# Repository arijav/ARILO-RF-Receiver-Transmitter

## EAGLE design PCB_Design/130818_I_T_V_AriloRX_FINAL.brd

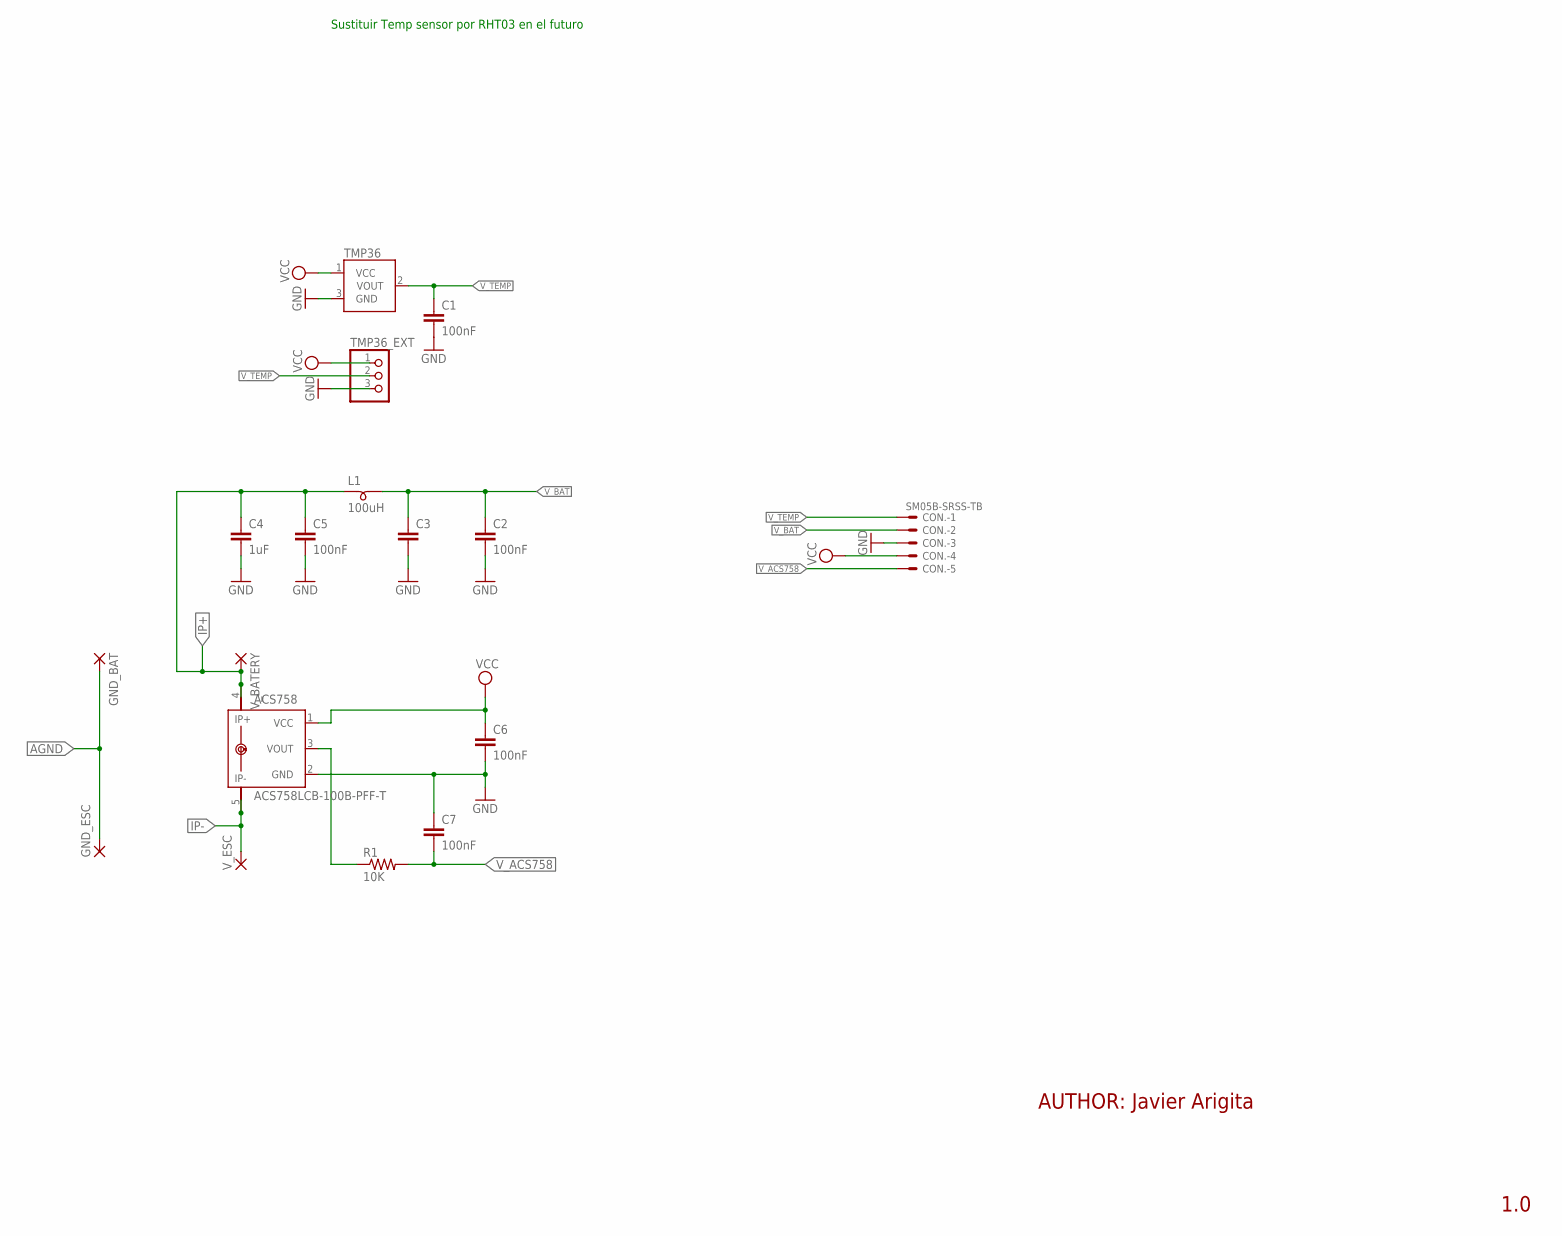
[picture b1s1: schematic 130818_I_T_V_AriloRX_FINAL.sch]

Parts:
ACS758: ACS758LCB-100B-PFF-T; CB-PFF
C1, C2, C5, C6, C7: 100nF; C0805
C3: C-EUC3216; C3216
C4: 1uF; C3216
CON.: SM05B-SRSS-TB
GND_BAT: SMD5; SMD2,54-5,08
GND_ESC: SMD5; SMD2,54-5,08
L1: 100uH; SM-B5
R1: 10K; R0805
TMP36: TMP36GT9; TO-92
TMP36_EXT: PINHD-1X3; 1X03
V_BATERY: SMD5; SMD2,54-5,08
V_ESC: SMD5; SMD2,54-5,08

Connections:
AGND: GND_BAT.1, GND_ESC.1
GND: ACS758.2 (GND), C1.2, C2.2, C3.2, C4.2, C5.2, C6.2, C7.1, CON..3, TMP36.3 (GND), TMP36_EXT.3
IP+: ACS758.4 (IP+), ACS758.IP+1, C4.1, C5.1, L1.1, V_BATERY.1
IP-: ACS758.5 (IP-), ACS758.IP-1, V_ESC.1
unnamed: ACS758.3 (VOUT), R1.1
VCC: ACS758.1 (VCC), C6.1, CON..4, TMP36.1 (VCC), TMP36_EXT.1
V_ACS758: C7.2, CON..5, R1.2
V_BAT: C2.1, C3.1, CON..2, L1.2
V_TEMP: C1.1, CON..1, TMP36.2 (VOUT), TMP36_EXT.2

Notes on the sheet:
AUTHOR: Javier Arigita
1.0
Sustituir Temp sensor por RHT03 en el futuro

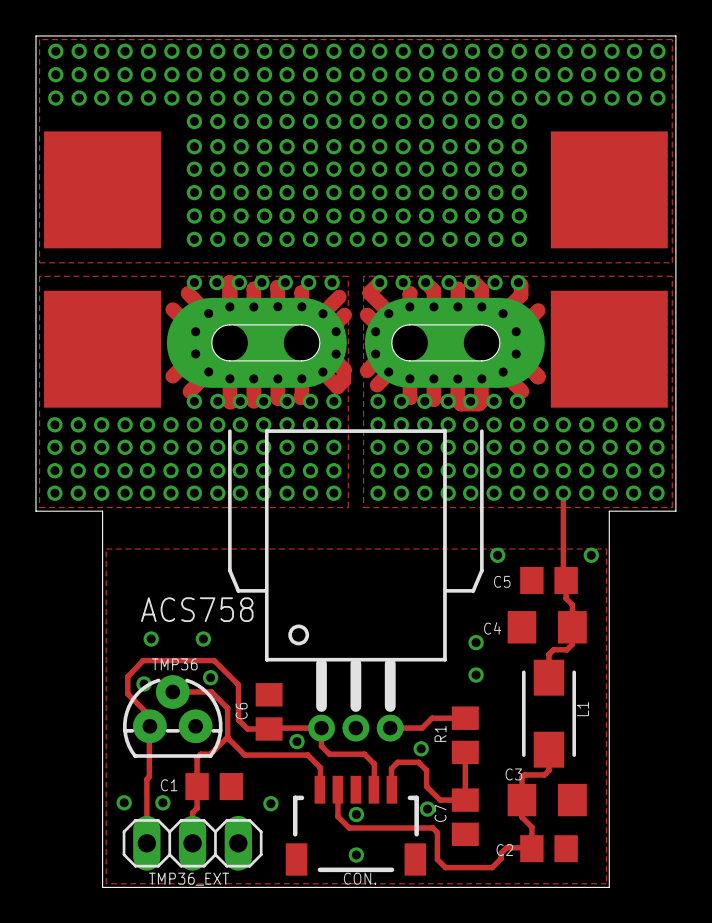
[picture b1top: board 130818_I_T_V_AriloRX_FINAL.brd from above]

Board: 2 copper layers, 35.6 x 47.3 mm, 17 parts (0 on the bottom side), 9 nets.

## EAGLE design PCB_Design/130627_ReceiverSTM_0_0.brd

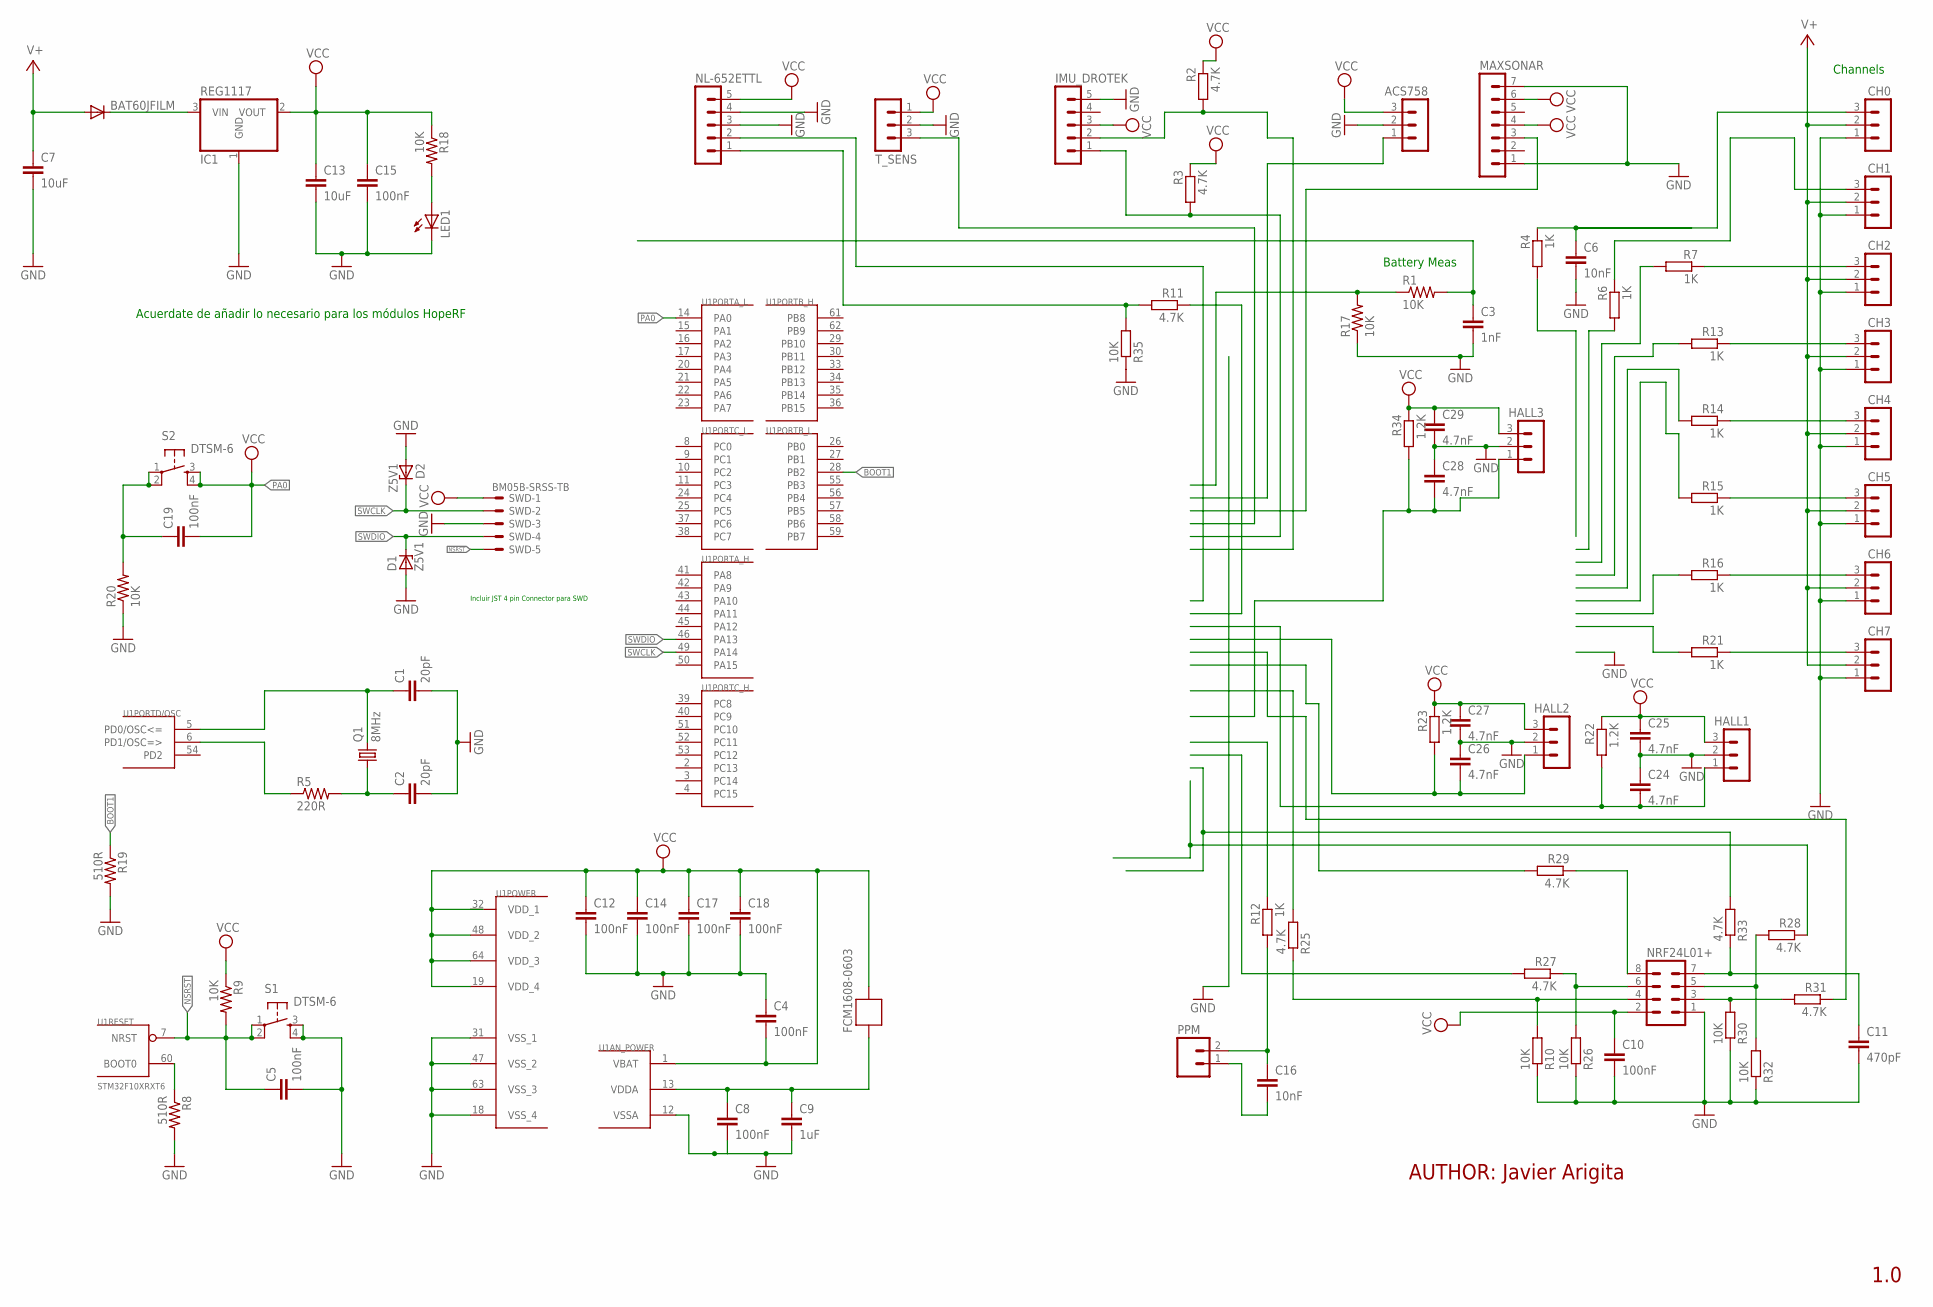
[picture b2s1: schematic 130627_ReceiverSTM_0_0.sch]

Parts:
ACS758: MA03-1
BAT60JFILM: DIODE-SOD323-R; SOD323-R
C1, C2: 20pF; C0805
C3: 1nF; C0805
C4, C5, C8, C10, C12, C14, C15, C17, C18, C19: 100nF; C0805
C6, C16: 10nF; C025-030X050
C7, C13: 10uF; C3216
C9: 1uF; C3216
C11: 470pF; C025-030X050
C24, C25, C26, C27, C28, C29: 4.7nF; C025-030X050
CH0, CH1, CH2, CH3, CH4, CH5, CH6, CH7: MA03-1
D1, D2: Z5V1; SOD80C
FCM1608-0603: FERRITE-BEAD; R0603
HALL1, HALL2, HALL3: MA03-1
IC1: REG1117; SOT223
IMU_DROTEK: MA05-1
LED1: LED0805; CHIPLED_0805
MAXSONAR: MA07-1
NL-652ETTL: MA05-1
NRF24L01+: MA04-2
PPM: M02; 02P
Q1: 8MHz; SM49
R1, R9, R17, R18, R20: 10K; R0805
R2, R3, R11, R25, R27, R28, R29, R31, R33: 4.7K; 0204/7
R4, R6, R7, R12, R13, R14, R15, R16, R21: 1K; 0204/7
R5: 220R; R0805
R8, R19: 510R; R0805
R10, R26, R30, R32, R35: 10K; 0204/7
R22, R23, R34: 1.2K; 0204/7
S1, S2: DTSM-6
SWD: BM05B-SRSS-TB
T_SENS: MA03-1
U1: STM32F10XRXT6; TQFP64

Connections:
BOOT1: R19.1, U1.28 (PB2)
GND: ACS758.2, C1.2, C2.2, C3.2, C4.1, C5.2, C6.2, C7.2, C8.2, C9.2, C10.2, C11.2, C12.2, C13.2, C14.2, C15.2, C17.2, C18.2, C24.1, C25.2, C26.1, C27.2, C28.1, C29.2, CH0.1, CH1.1, CH2.1, CH3.1, CH4.1, CH5.1, CH6.1, CH7.1, D1.A, D2.A, HALL1.2, HALL2.2, HALL3.2, IC1.1 (GND), IMU_DROTEK.5, LED1.C, MAXSONAR.1, MAXSONAR.7, NL-652ETTL.3, NL-652ETTL.4, NRF24L01+.1, R8.2, R10.1, R17.1, R19.2, R20.1, R26.1, R30.1, R32.1, R35.1, S1.3, S1.4, T_SENS.2, U1.12 (VSSA), U1.18 (VSS_4), U1.31 (VSS_1), U1.47 (VSS_2), U1.63 (VSS_3)
MAX_BRIDGE: NL-652ETTL.2
unnamed: C1.1, Q1.2, U1.5 (PD0/OSC<=)
unnamed: R5.1, U1.6 (PD1/OSC=>)
unnamed: C2.1, Q1.1, R5.2
unnamed: R8.1, U1.60 (BOOT0)
unnamed: C19.1, R20.2, S2.1, S2.2
unnamed: ACS758.3, C25.1, C27.1, C29.1, HALL1.3, HALL2.3, HALL3.3, IMU_DROTEK.3, MAXSONAR.4, MAXSONAR.6, NL-652ETTL.5, R2.1, R3.1, R22.1, R23.1, R34.1, T_SENS.1
unnamed: C16.2, PPM.1
unnamed: IMU_DROTEK.2, R2.2
unnamed: LED1.A, R18.2
unnamed: C28.2, HALL3.1, R34.2
unnamed: BAT60JFILM.C, IC1.3 (VIN)
unnamed: C24.2, HALL1.1, R22.2
unnamed: C3.1, R1.2
unnamed: C8.1, C9.1, FCM1608-0603.2, U1.13 (VDDA)
unnamed: NRF24L01+.4, R10.2, R25.1
unnamed: NRF24L01+.3, R30.2, R31.2
unnamed: C16.1, PPM.2, R12.2
unnamed: NL-652ETTL.1, R11.2, R35.2
unnamed: IMU_DROTEK.1, R3.2
unnamed: C26.2, HALL2.1, R23.2
unnamed: R1.1, R17.2
unnamed: NRF24L01+.8, R29.1
unnamed: NRF24L01+.6, R26.2, R27.1
unnamed: NRF24L01+.5, R28.2, R32.2
unnamed: C11.1, NRF24L01+.7, R33.1
unnamed: C6.1, CH0.3, R4.1
unnamed: CH1.3, R6.1
unnamed: CH2.3, R7.1
unnamed: CH3.3, R13.1
unnamed: CH4.3, R14.1
unnamed: CH5.3, R15.1
unnamed: CH6.3, R16.1
unnamed: CH7.3, R21.1
NSRST: C5.1, R9.2, S1.1, S1.2, SWD.5, U1.7 (NRST)
PA0: C4.2, C10.1, C12.1, C13.1, C14.1, C15.1, C17.1, C18.1, C19.2, FCM1608-0603.1, IC1.2 (VOUT), NRF24L01+.2, R9.1, R18.1, S2.3, S2.4, U1.1 (VBAT), U1.14 (PA0), U1.19 (VDD_4), U1.48 (VDD_2), U1.64 (VDD_3)
SWCLK: D2.C, SWD.2, SWD.3, U1.49 (PA14)
SWDIO: D1.C, SWD.4, U1.46 (PA13)
V+: BAT60JFILM.A, C7.1, CH0.2, CH1.2, CH2.2, CH3.2, CH4.2, CH5.2, CH6.2, CH7.2
VCC: SWD.1
VDD_1: U1.32 (VDD_1)

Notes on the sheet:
Battery Meas
Acuerdate de añadir lo necesario para los módulos HopeRF
AUTHOR: Javier Arigita
1.0
Channels
Incluir JST 4 pin Connector para SWD

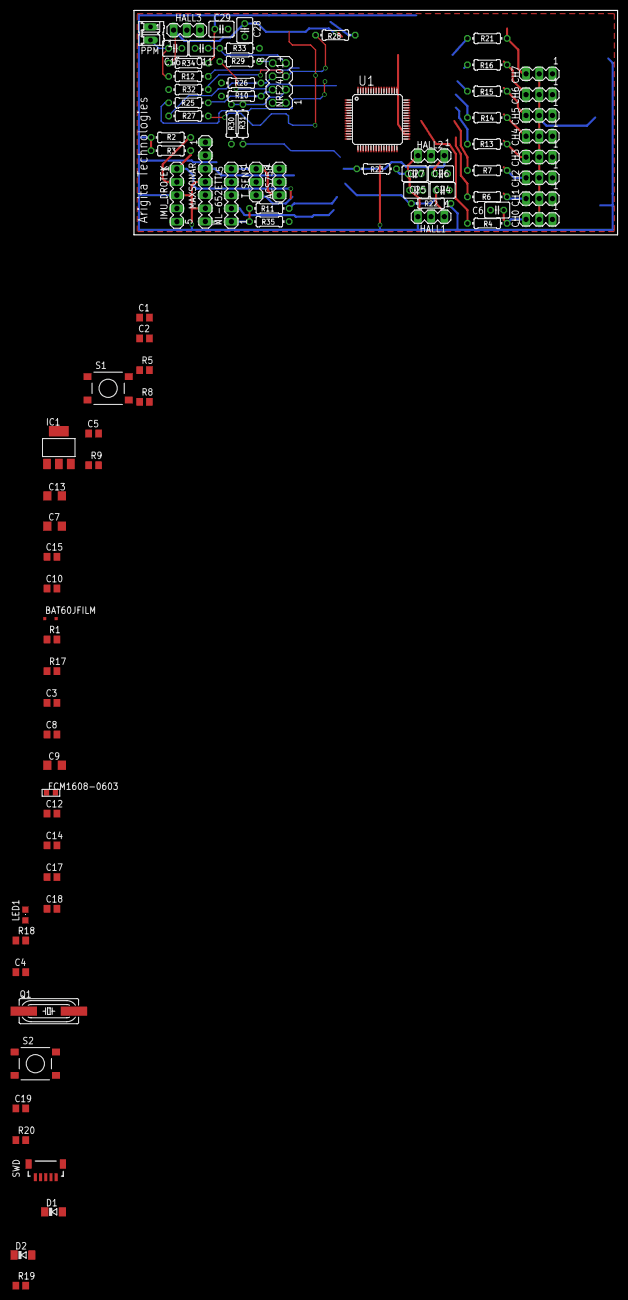
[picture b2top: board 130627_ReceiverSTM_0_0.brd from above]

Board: 2 copper layers, 93.0 x 43.2 mm, 88 parts (0 on the bottom side), 40 nets.

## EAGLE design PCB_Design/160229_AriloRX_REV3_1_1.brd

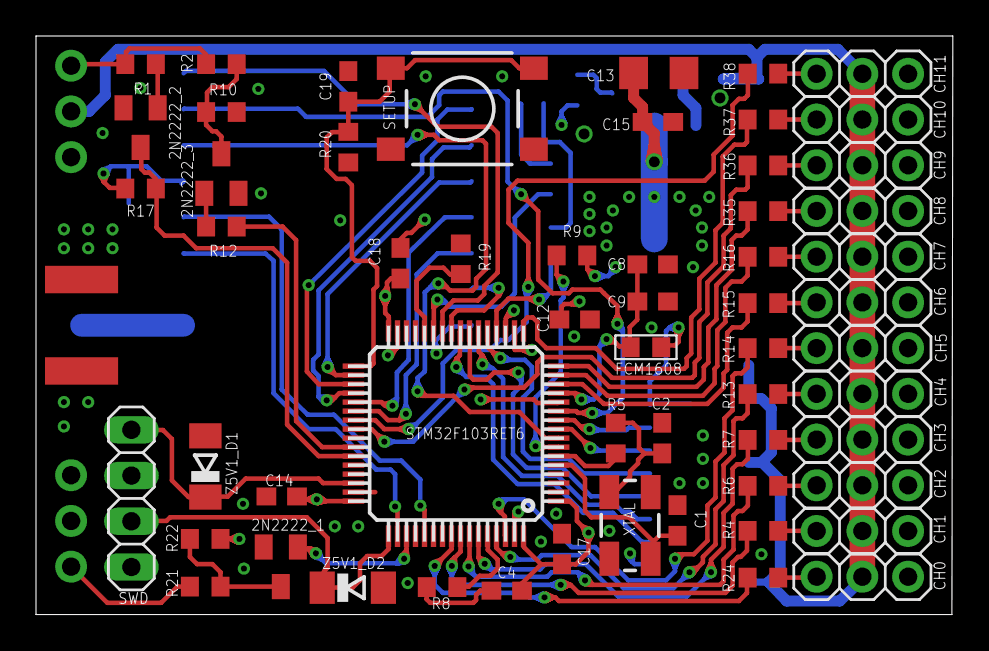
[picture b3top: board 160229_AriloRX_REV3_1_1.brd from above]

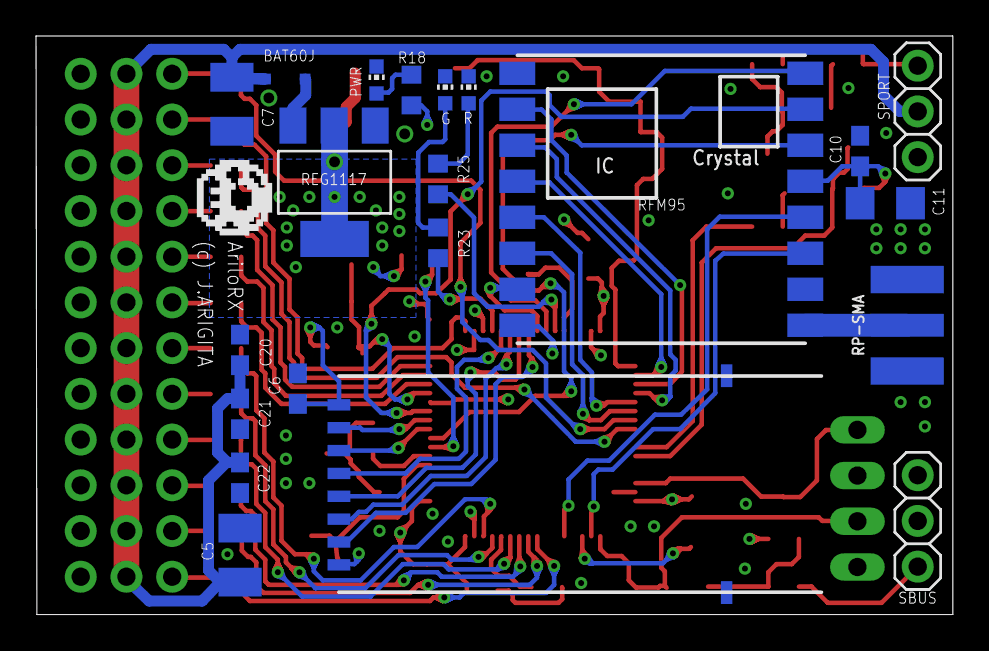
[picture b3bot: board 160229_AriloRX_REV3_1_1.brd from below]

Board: 4 copper layers, 50.9 x 32.1 mm, 79 parts (21 on the bottom side), 70 nets.

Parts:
2N2222_1, 2N2222_2, 2N2222_3: SOT23-BEC
BAT60J: SOD323-R
C1, C2: 12pF; RESISTOR_C0603
C4, C6, C8, C10, C12, C14, C15, C17, C18, C19, C20: 100nF; RESISTOR_C0603
C5: SMC_B
C7: 100uF; SMC_B
C9: 1uF; RESISTOR_C0603
C11, C13: 10uF; RESISTOR_C3216
C21: 10nF; RESISTOR_C0603
C22: 1nF; RESISTOR_C0603
CH0, CH1, CH2, CH3, CH4, CH5, CH6, CH7, CH8, CH9, CH10, CH11: 1X03
FCM1608: R0603
G: CHIP-LED0603
NRF24L01_SMD: NRF24L01+_NRF24L01_SMDSMD; NRF24L01+_NRF24L01_SMD
PWR: LED_CHIP-LED0603
R: CHIP-LED0603
R1, R9, R18, R20: 10K; RCL_R0603
R2, R4, R6, R7, R10, R12, R13, R14, R15, R16, R21, R22, R24, R35, R36, R37, R38: 1K; RCL_R0603
R5: 80R; RCL_R0603
R8, R19: 510R; RCL_R0603
R17: 4.7K; RCL_R0603
R23, R25: 220; RCL_R0603
REG1117: REG1117; SOT223
RFM95: RFM95W_MISIEK_RFM95WSMD; RFM95W_MISIEK_RFM95W_SMD
RP-SMA: SMA_EDGELAUNCH
SBUS: 1X03
SETUP: DTSM-6
SPORT: 1X03
STM32F103RET6: STM32F103RET6; TQFP64
SWD: 1X04
XTAL: 12MHz; CRYSTAL-SMD-5X3
Z5V1_D1, Z5V1_D2: Z5V1; SOD80C

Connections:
BOOT1: R19.1, STM32F103RET6.28
CH0: R24.2, STM32F103RET6.56
CH1: R4.2, STM32F103RET6.57
CH2: R6.2, STM32F103RET6.58
CH3: R7.2, STM32F103RET6.59
CH4: R13.2, STM32F103RET6.61
CH5: R14.2, STM32F103RET6.62
CH6: R15.2, STM32F103RET6.14
CH7: R16.2, STM32F103RET6.15
CH8: R35.2, STM32F103RET6.16
CH9: R36.2, STM32F103RET6.40
CH10: R37.2, STM32F103RET6.17
CH11: R38.2, STM32F103RET6.39
GND: 2N2222_1.E, 2N2222_2.E, 2N2222_3.E, C1.2, C2.2, C4.1, C5.-, C6.2, C7.-, C8.2, C9.2, C10.2, C11.2, C12.2, C13.2, C14.2, C15.2, C17.2, C18.2, C19.1, C20.2, C21.2, C22.2, CH0.1, CH1.1, CH2.1, CH3.1, CH4.1, CH5.1, CH6.1, CH7.1, CH8.1, CH9.1, CH10.1, CH11.1, G.C, NRF24L01_SMD.P$1, PWR.C, R.C, R8.2, R19.2, REG1117.1, RFM95.1, RFM95.8, RFM95.10, RP-SMA.GND@1, RP-SMA.GND@2, RP-SMA.GND@3, RP-SMA.GND@4, SBUS.3, SETUP.1, SETUP.2, SPORT.3, STM32F103RET6.12, STM32F103RET6.18, STM32F103RET6.31, STM32F103RET6.47, STM32F103RET6.63, SWD.3, Z5V1_D1.A, Z5V1_D2.A
HOPERF_CSN: RFM95.5, STM32F103RET6.37
HOPERF_DIO0: RFM95.14, STM32F103RET6.8
HOPERF_DIO1: RFM95.15, STM32F103RET6.11
HOPERF_DIO2: RFM95.16, STM32F103RET6.26
HOPERF_DIO3: RFM95.11, STM32F103RET6.50
HOPERF_DIO4: RFM95.12, STM32F103RET6.53
HOPERF_DIO5: RFM95.7, STM32F103RET6.25
HOPERF_RESET: RFM95.6, STM32F103RET6.38
INP_1: C19.2, R20.1, SETUP.3, SETUP.4, STM32F103RET6.33
LED_GREEN: R23.2, STM32F103RET6.20
LED_RED: R25.2, STM32F103RET6.27
unnamed: C1.1, STM32F103RET6.5, XTAL.3
unnamed: R5.1, STM32F103RET6.6
unnamed: C2.1, R5.2, XTAL.1
unnamed: R8.1, STM32F103RET6.60
unnamed: 2N2222_3.C, R2.2, R10.2
unnamed: RFM95.9, RP-SMA.P
unnamed: 2N2222_3.B, R12.1
unnamed: CH0.3, R24.1
unnamed: PWR.A, R18.2
unnamed: 2N2222_1.C, R21.2, R22.2
unnamed: G.A, R23.1
unnamed: CH8.3, R35.1
unnamed: R1.1, R2.1, SPORT.1
unnamed: R.A, R25.1
unnamed: 2N2222_2.B, R1.2
unnamed: C8.1, C9.1, FCM1608.2, STM32F103RET6.13
unnamed: CH2.3, R6.1
unnamed: CH4.3, R13.1
unnamed: CH9.3, R36.1
unnamed: CH10.3, R37.1
unnamed: CH11.3, R38.1
unnamed: CH3.3, R7.1
unnamed: CH6.3, R15.1
unnamed: CH5.3, R14.1
unnamed: CH7.3, R16.1
unnamed: CH1.3, R4.1
NRF_CE: NRF24L01_SMD.P$7, STM32F103RET6.10
NRF_CSN: NRF24L01_SMD.P$6, STM32F103RET6.9
NRF_IRQ: NRF24L01_SMD.P$2, STM32F103RET6.24
NSRST: R9.2, STM32F103RET6.7
SBUS: R21.1, SBUS.1
SPI1_MISO: NRF24L01_SMD.P$3, STM32F103RET6.22
SPI1_MOSI: NRF24L01_SMD.P$4, STM32F103RET6.23
SPI1_SCK: NRF24L01_SMD.P$5, STM32F103RET6.21
SPI2_MISO: RFM95.2, STM32F103RET6.35
SPI2_MOSI: RFM95.3, STM32F103RET6.36
SPI2_SCK: RFM95.4, STM32F103RET6.34
SWCLK: STM32F103RET6.49, SWD.2, Z5V1_D2.C
SWDIO: STM32F103RET6.46, SWD.4, Z5V1_D1.C
USART1_RX: 2N2222_2.C, R17.2, STM32F103RET6.43
USART1_TX: R12.2, STM32F103RET6.42
USART3_TX: 2N2222_1.B, STM32F103RET6.51
V+: BAT60J.A, C5.+, C7.+, C20.1, C21.1, C22.1, CH0.2, CH1.2, CH2.2, CH3.2, CH4.2, CH5.2, CH6.2, CH7.2, CH8.2, CH9.2, CH10.2, CH11.2, SBUS.2, SPORT.2
VCC: C4.2, C6.1, C10.1, C11.1, C12.1, C13.1, C14.1, C15.1, C17.1, C18.1, FCM1608.1, NRF24L01_SMD.P$8, R9.1, R10.1, R17.1, R18.1, R20.2, R22.1, REG1117.2, REG1117.4, RFM95.13, STM32F103RET6.1, STM32F103RET6.19, STM32F103RET6.32, STM32F103RET6.48, STM32F103RET6.64, SWD.1
VDD: BAT60J.C, REG1117.3

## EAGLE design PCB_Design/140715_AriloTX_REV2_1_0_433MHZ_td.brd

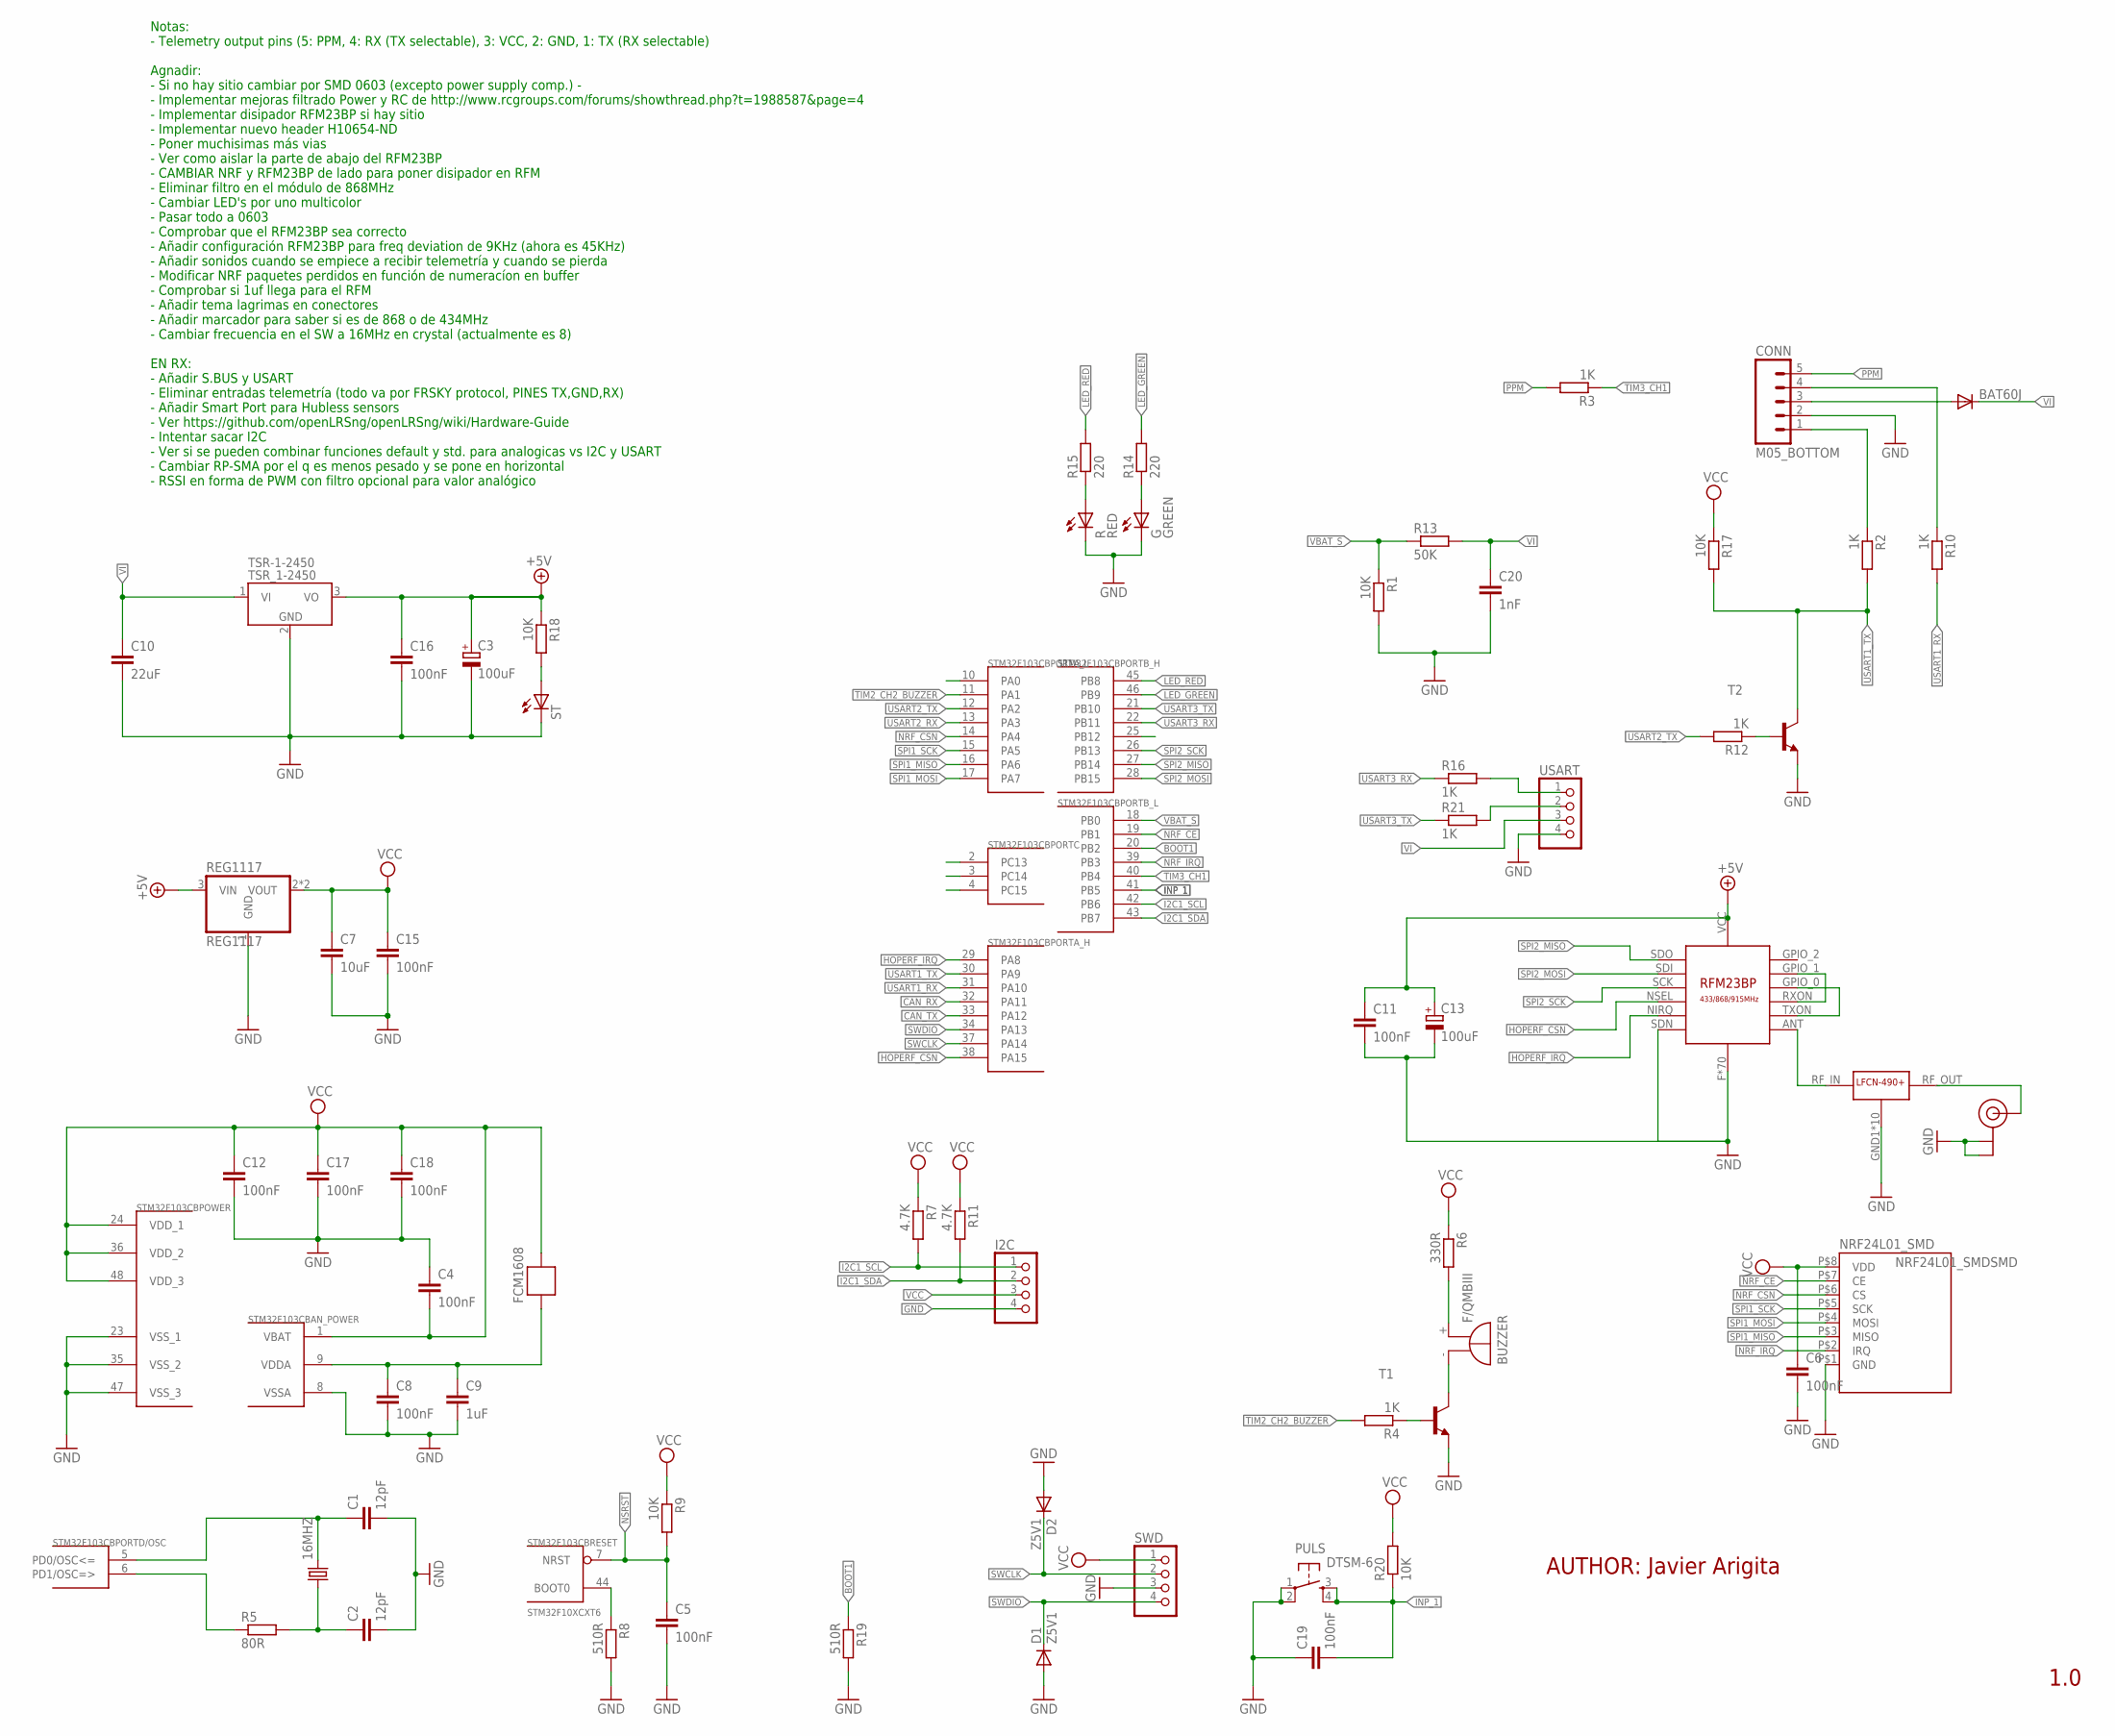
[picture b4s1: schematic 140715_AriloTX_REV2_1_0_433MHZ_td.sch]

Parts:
16MHZ: CRYSTAL5X3; CRYSTAL-SMD-5X3
BAT60J: DIODE-SOD323-R; SOD323-R
BUZZER: F/QMBIII
C1, C2: 12pF; C0603
C3, C13: 100uF; SMC_B
C4, C5, C6, C8, C11, C12, C15, C16, C17, C18, C19: 100nF; C0603
C7: 10uF; C0805
C9: 1uF; C0603
C10: 22uF; C3216
C20: 1nF; C0603
CONN: M05_BOTTOM
D1, D2: Z5V1; SOD323-R
FCM1608: FERRITE-BEAD; R0603
G: GREEN; CHIP-LED0603
I2C: PINHD-1X4; 1X04
LFCN490+: LFCN490+
NRF24L01_SMD: NRF24L01_SMDSMD; NRF24L01_SMD
PULS: DTSM-6
R: RED; CHIP-LED0603
R1, R9, R17, R18, R20: 10K; R0603
R2, R3, R4, R10, R12, R16, R21: 1K; R0603
R5: 80R; R0603
R6: 330R; R0603
R7, R11: 4.7K; R0603
R8, R19: 510R; R0603
R13: 50K; R0603
R14, R15: 220; R0603
REG1117: REG1117; SOT223
ST: LEDCHIP-LED0603; CHIP-LED0603
STM32F103CB: STM32F10XCXT6; TQFP48
SWD: PINHD-1X4; 1X04
T1, T2: BC848-NPN-SOT23-BEC; SOT23-BEC
TSR-1-2450: TSR_1-2450; TSR-1
U$1: RFM23BP
U.FL: U.FL
USART: PINHD-1X4; 1X04

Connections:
+5V: C3.+, C11.1, C13.+, C16.1, R18.1, REG1117.3 (VIN), TSR-1-2450.3 (VO), U$1.VCC
BOOT1: R19.1, STM32F103CB.20 (PB2)
CAN_RX: STM32F103CB.32 (PA11)
CAN_TX: STM32F103CB.33 (PA12)
GND: C1.2, C2.2, C3.-, C4.1, C5.2, C6.2, C7.2, C8.2, C9.2, C10.2, C11.2, C12.2, C13.-, C15.2, C16.2, C17.2, C18.2, C19.1, C20.2, CONN.2, D1.A, D2.A, G.C, I2C.4, LFCN490+.GND1 (GND), LFCN490+.GND2 (GND), LFCN490+.GND3 (GND), LFCN490+.GND4 (GND), LFCN490+.GND5 (GND), LFCN490+.GND6 (GND), LFCN490+.GND7 (GND), LFCN490+.GND8 (GND), LFCN490+.GND9 (GND), LFCN490+.GND10 (GND), NRF24L01_SMD.P$1 (GND), PULS.1, PULS.2, R.C, R1.2, R8.2, R19.2, REG1117.1 (GND), ST.C, STM32F103CB.8 (VSSA), STM32F103CB.23 (VSS_1), STM32F103CB.35 (VSS_2), STM32F103CB.47 (VSS_3), SWD.3, T1.E, T2.E, TSR-1-2450.2 (GND), U$1.F (GND), U$1.F1 (GND), U$1.F2 (GND), U$1.F3 (GND), U$1.F4 (GND), U$1.F5 (GND), U$1.F6 (GND), U$1.F7 (GND), U$1.F8 (GND), U$1.F9 (GND), U$1.F10 (GND), U$1.F11 (GND), U$1.F12 (GND), U$1.F13 (GND), U$1.F14 (GND), U$1.F15 (GND), U$1.F16 (GND), U$1.F17 (GND), U$1.F18 (GND), U$1.F19 (GND), U$1.F20 (GND), U$1.F21 (GND), U$1.F22 (GND), U$1.F23 (GND), U$1.F24 (GND), U$1.F25 (GND), U$1.F26 (GND), U$1.F27 (GND), U$1.F28 (GND), U$1.F29 (GND), U$1.F30 (GND), U$1.F31 (GND), U$1.F32 (GND), U$1.F33 (GND), U$1.F34 (GND), U$1.F35 (GND), U$1.F36 (GND), U$1.F37 (GND), U$1.F38 (GND), U$1.F39 (GND), U$1.F40 (GND), U$1.F41 (GND), U$1.F42 (GND), U$1.F43 (GND), U$1.F44 (GND), U$1.F45 (GND), U$1.F46 (GND), U$1.F47 (GND), U$1.F48 (GND), U$1.F49 (GND), U$1.F50 (GND), U$1.F51 (GND), U$1.F52 (GND), U$1.F53 (GND), U$1.F54 (GND), U$1.F55 (GND), U$1.F56 (GND), U$1.F57 (GND), U$1.F58 (GND), U$1.F59 (GND), U$1.F60 (GND), U$1.F61 (GND), U$1.F62 (GND), U$1.F63 (GND), U$1.F64 (GND), U$1.F65 (GND), U$1.GND1 (GND), U$1.GND2 (GND), U$1.GND3 (GND), U$1.GND_HEAT (GND), U$1.SDN, U.FL.P$1 (GND), U.FL.P$2 (GND), USART.4
HOPERF_CSN: STM32F103CB.38 (PA15), U$1.NSEL
HOPERF_IRQ: STM32F103CB.29 (PA8), U$1.NIRQ
I2C1_SCL: I2C.1, R7.2, STM32F103CB.42 (PB6)
I2C1_SDA: I2C.2, R11.2, STM32F103CB.43 (PB7)
INP_1: C19.2, PULS.3, PULS.4, R20.1, STM32F103CB.41 (PB5)
LED_GREEN: R14.2, STM32F103CB.46 (PB9)
LED_RED: R15.2, STM32F103CB.45 (PB8)
unnamed: 16MHZ.3 (2), C1.1, STM32F103CB.5 (PD0/OSC<=)
unnamed: R5.1, STM32F103CB.6 (PD1/OSC=>)
unnamed: 16MHZ.1, C2.1, R5.2
unnamed: R8.1, STM32F103CB.44 (BOOT0)
unnamed: R12.1, T2.B
unnamed: CONN.1, R2.1
unnamed: R.A, R15.1
unnamed: G.A, R14.1
unnamed: CONN.4, R10.1
unnamed: R18.2, ST.A
unnamed: LFCN490+.RF_IN (RF_INP), U$1.ANT
unnamed: R16.2, USART.1
unnamed: R21.2, USART.2
unnamed: BAT60J.A, CONN.3
unnamed: BUZZER.+ (-), R6.2
unnamed: C8.1, C9.1, FCM1608.2, STM32F103CB.9 (VDDA)
unnamed: LFCN490+.RF_OUT (RF_OUTP), U.FL.P$3 (SIGNAL)
unnamed: R4.1, T1.B
unnamed: BUZZER.- (+), T1.C
unnamed: U$1.GPIO_1, U$1.RXON
unnamed: U$1.GPIO_0, U$1.TXON
NRF_CE: NRF24L01_SMD.P$7 (CE), STM32F103CB.19 (PB1)
NRF_CSN: NRF24L01_SMD.P$6 (CS), STM32F103CB.14 (PA4)
NRF_IRQ: NRF24L01_SMD.P$2 (IRQ), STM32F103CB.39 (PB3)
NSRST: C5.1, R9.2, STM32F103CB.7 (NRST)
PPM: CONN.5, R3.2
SPI1_MISO: NRF24L01_SMD.P$3 (MISO), STM32F103CB.16 (PA6)
SPI1_MOSI: NRF24L01_SMD.P$4 (MOSI), STM32F103CB.17 (PA7)
SPI1_SCK: NRF24L01_SMD.P$5 (SCK), STM32F103CB.15 (PA5)
SPI2_MISO: STM32F103CB.27 (PB14), U$1.SDO
SPI2_MOSI: STM32F103CB.28 (PB15), U$1.SDI
SPI2_SCK: STM32F103CB.26 (PB13), U$1.SCK
SWCLK: D2.C, STM32F103CB.37 (PA14), SWD.2
SWDIO: D1.C, STM32F103CB.34 (PA13), SWD.4
TIM2_CH2_BUZZER: R4.2, STM32F103CB.11 (PA1)
TIM3_CH1: R3.1, STM32F103CB.40 (PB4)
USART1_RX: R10.2, STM32F103CB.31 (PA10)
USART1_TX: R2.2, R17.2, STM32F103CB.30 (PA9), T2.C
USART2_RX: STM32F103CB.13 (PA3)
USART2_TX: R12.2, STM32F103CB.12 (PA2)
USART3_RX: R16.1, STM32F103CB.22 (PB11)
USART3_TX: R21.1, STM32F103CB.21 (PB10)
VBAT_S: R1.1, R13.1, STM32F103CB.18 (PB0)
VCC: C4.2, C6.1, C7.1, C12.1, C15.1, C17.1, C18.1, FCM1608.1, I2C.3, NRF24L01_SMD.P$8 (VDD), R6.1, R7.1, R9.1, R11.1, R17.1, R20.2, REG1117.2 (VOUT), REG1117.4 (VOUT), STM32F103CB.1 (VBAT), STM32F103CB.24 (VDD_1), STM32F103CB.36 (VDD_2), STM32F103CB.48 (VDD_3), SWD.1
VI: BAT60J.C, C10.1, C20.1, R13.2, TSR-1-2450.1 (VI), USART.3

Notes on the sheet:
AUTHOR: Javier Arigita
1.0
Notas: - Telemetry output pins (5: PPM, 4: RX (TX selectable), 3: VCC, 2: GND, 1: TX (RX selectable) Agnadir: - Si no hay sitio cambiar por SMD 0603 (excepto power supply comp.) - - Implementar mejoras filtrado Power y RC de http://www.rcgroups.com/forums/showthread.php?t=1988587&page=4 - Implement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

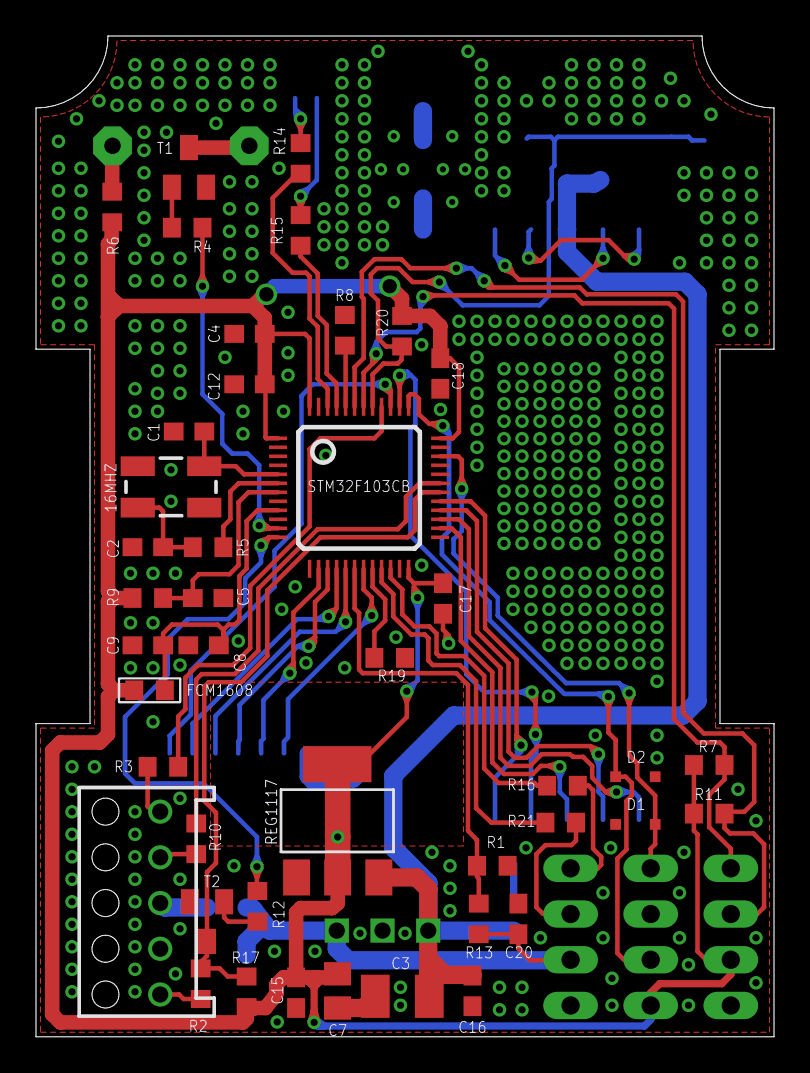
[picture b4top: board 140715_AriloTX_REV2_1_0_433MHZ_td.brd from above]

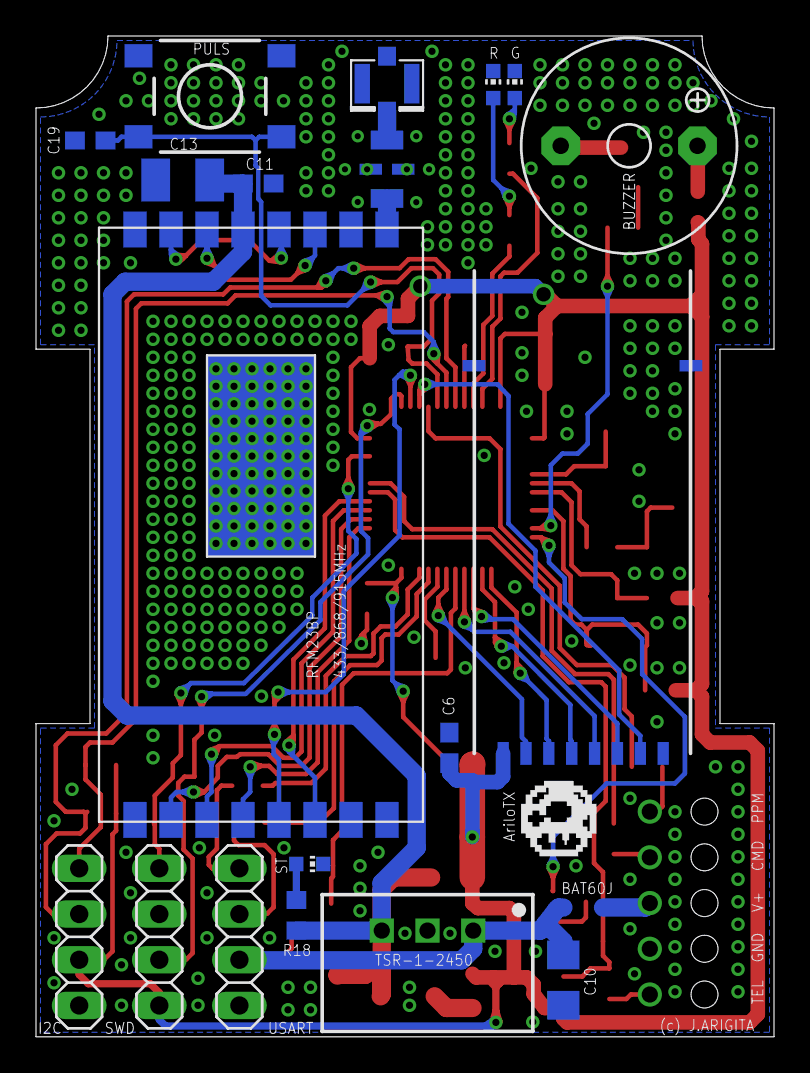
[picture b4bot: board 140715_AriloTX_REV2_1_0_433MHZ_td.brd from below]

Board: 2 copper layers, 41.0 x 55.6 mm, 63 parts (20 on the bottom side), 54 nets.

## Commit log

2020-05-03 Initial commit of Arilo RX/TX projects
2020-05-03 PCB design for Arilo RX/TX

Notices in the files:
parts and their libraries:
SparkFun-Sensors: Licensing: CC v3.0 Share-Alike You are welcome to use this library for commercial purposes.
